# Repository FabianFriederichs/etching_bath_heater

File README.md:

# etching_bath_heater
An AVR 8-Bit µC based etching bath controller including PID controlled heater and agitation.

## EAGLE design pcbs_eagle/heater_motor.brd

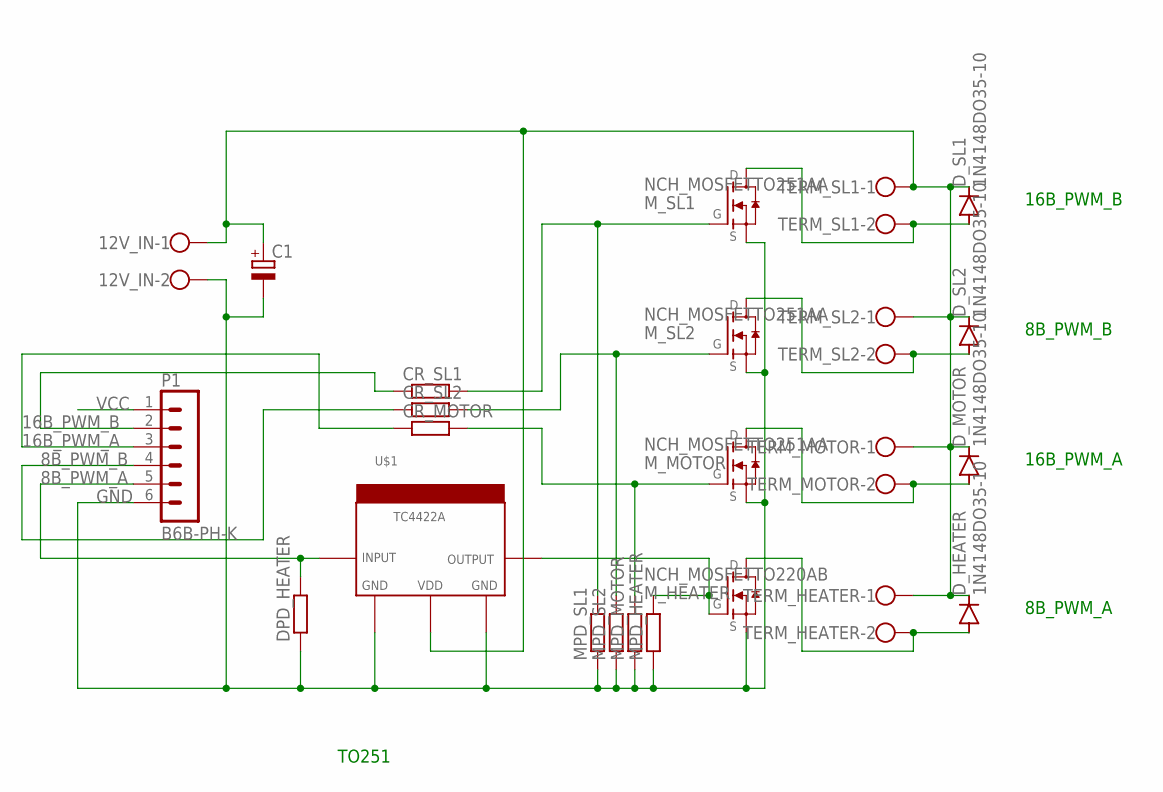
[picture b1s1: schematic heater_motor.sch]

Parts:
12V_IN: W237-102
C1: CPOL-EUE5-10.5; E5-10,5
CR_MOTOR: R-EU_0207/10; 0207/10
CR_SL1, CR_SL2: R-EU_0207/10; 0207/10
DPD_HEATER: R-EU_0207/10; 0207/10
D_HEATER: 1N4148DO35-10; DO35-10
D_MOTOR: 1N4148DO35-10; DO35-10
D_SL1, D_SL2: 1N4148DO35-10; DO35-10
MPD_HEATER: R-EU_0207/10; 0207/10
MPD_MOTOR: R-EU_0207/10; 0207/10
MPD_SL1, MPD_SL2: R-EU_0207/10; 0207/10
M_HEATER: NCH_MOSFETTO220AB; TO220AB
M_MOTOR: NCH_MOSFETTO251AA; TO251AA
M_SL1, M_SL2: NCH_MOSFETTO251AA; TO251AA
P1: B6B-PH-K
TERM_HEATER: W237-102
TERM_MOTOR: W237-102
TERM_SL1, TERM_SL2: W237-102
U$1: TC4422ASPACE_LEGS; TO220-52

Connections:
8B_PWM_A: DPD_HEATER.2, P1.5, U$1.1 (INPUT)
8B_PWM_B: CR_SL2.1, P1.4
16B_PWM_A: CR_MOTOR.1, P1.3
16B_PWM_B: CR_SL1.1, P1.2
GND: 12V_IN.2, C1.-, DPD_HEATER.1, MPD_HEATER.1, MPD_MOTOR.1, MPD_SL1.1, MPD_SL2.1, M_HEATER.3 (S), M_MOTOR.3 (S), M_SL1.3 (S), M_SL2.3 (S), P1.6, U$1.2 (GND1), U$1.4 (GND2)
unnamed: D_HEATER.A, M_HEATER.2 (D), TERM_HEATER.2
unnamed: MPD_HEATER.2, M_HEATER.1 (G), U$1.5 (OUTPUT)
unnamed: D_SL1.A, M_SL1.2 (D), TERM_SL1.2
unnamed: D_SL2.A, M_SL2.2 (D), TERM_SL2.2
unnamed: D_MOTOR.A, M_MOTOR.2 (D), TERM_MOTOR.2
unnamed: CR_MOTOR.2, MPD_MOTOR.2, M_MOTOR.1 (G)
unnamed: CR_SL2.2, MPD_SL2.2, M_SL2.1 (G)
unnamed: CR_SL1.2, MPD_SL1.2, M_SL1.1 (G)
unnamed: 12V_IN.1, C1.+, D_HEATER.C, D_MOTOR.C, D_SL1.C, D_SL2.C, TERM_HEATER.1, TERM_MOTOR.1, TERM_SL1.1, TERM_SL2.1, U$1.3 (VDD)
VCC: P1.1

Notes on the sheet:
TO251
8B_PWM_A
8B_PWM_B
16B_PWM_A
16B_PWM_B

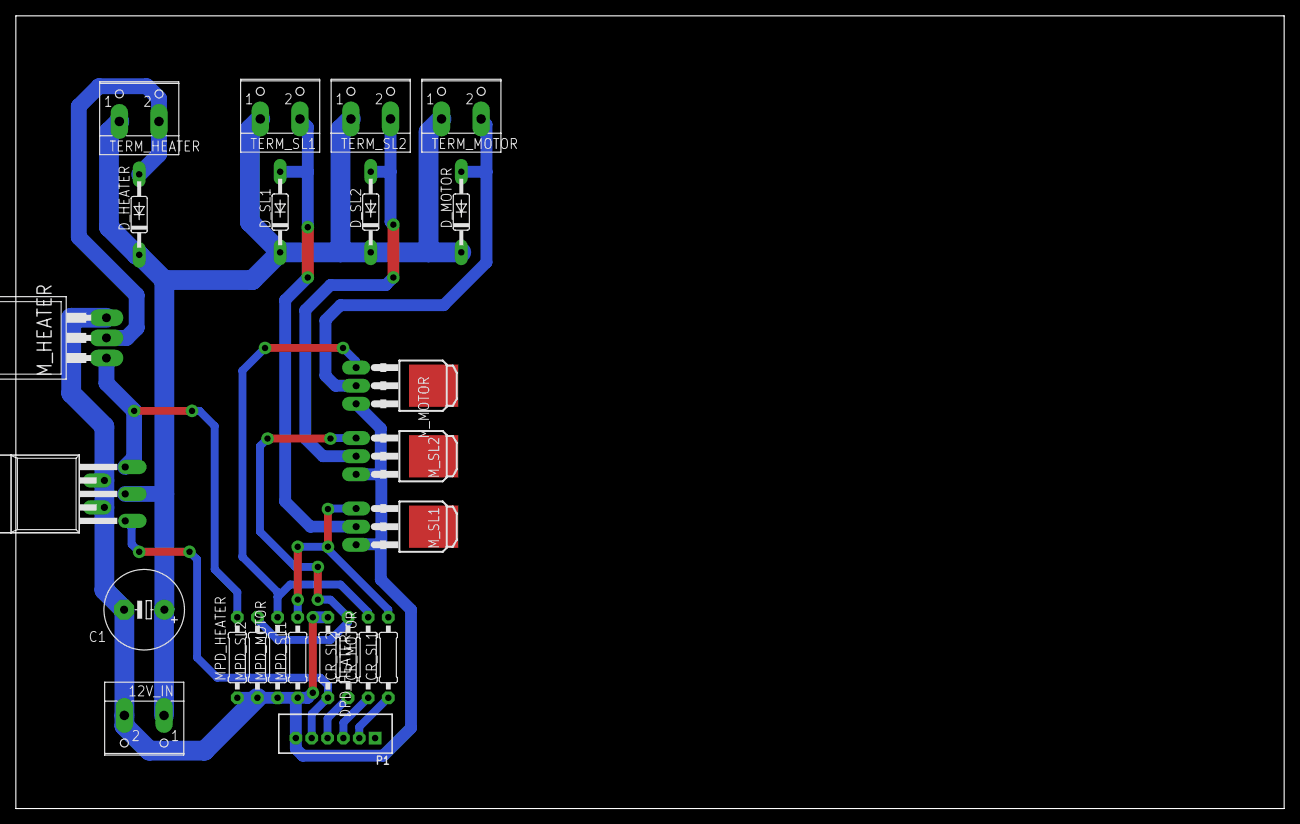
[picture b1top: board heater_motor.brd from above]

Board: 2 copper layers, 160.0 x 100.0 mm, 24 parts (0 on the bottom side), 14 nets.

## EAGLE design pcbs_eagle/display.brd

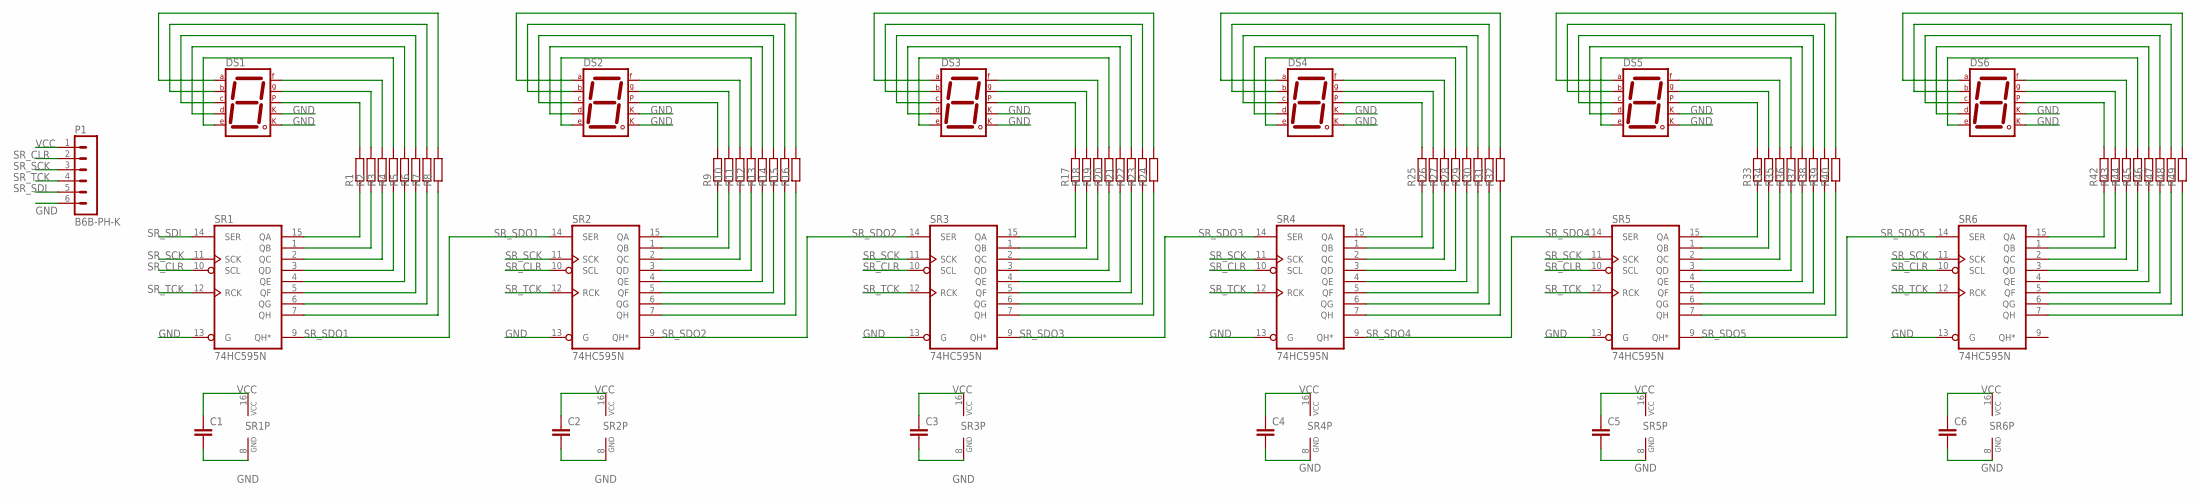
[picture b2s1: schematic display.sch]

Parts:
C1, C2, C3, C4, C5, C6: C-EU025-024X044; C025-024X044
DS1, DS2, DS3, DS4, DS5, DS6: 7SEG-CK; 7SEG-13
P1: B6B-PH-K
R1, R2, R3, R4, R5, R6, R7, R8, R9, R10, R11, R12, R13, R14, R15, R16, R17, R18, R19, R20, R21, R22, R23, R24, R25, R26, R27, R28, R29, R30, R31, R32, R33, R34, R35, R36, R37, R38, R39, R40, R42, R43, R44, R45, R46, R47, R48, R49: R-EU_0207/10; 0207/10
SR1, SR2, SR3, SR4, SR5, SR6: 74HC595N; DIL16

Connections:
GND: C1.2, C2.2, C3.2, C4.2, C5.2, C6.2, DS1.3 (CK1), DS1.8 (CK2), DS2.3 (CK1), DS2.8 (CK2), DS3.3 (CK1), DS3.8 (CK2), DS4.3 (CK1), DS4.8 (CK2), DS5.3 (CK1), DS5.8 (CK2), DS6.3 (CK1), DS6.8 (CK2), P1.6, SR1.8 (GND), SR1.13 (G), SR2.8 (GND), SR2.13 (G), SR3.8 (GND), SR3.13 (G), SR4.8 (GND), SR4.13 (G), SR5.8 (GND), SR5.13 (G), SR6.8 (GND), SR6.13 (G)
unnamed: R1.1, SR1.15 (QA)
unnamed: R2.1, SR1.1 (QB)
unnamed: R3.1, SR1.2 (QC)
unnamed: R4.1, SR1.3 (QD)
unnamed: R5.1, SR1.4 (QE)
unnamed: R6.1, SR1.5 (QF)
unnamed: R7.1, SR1.6 (QG)
unnamed: R8.1, SR1.7 (QH)
unnamed: R9.1, SR2.15 (QA)
unnamed: R10.1, SR2.1 (QB)
unnamed: R11.1, SR2.2 (QC)
unnamed: R12.1, SR2.3 (QD)
unnamed: R13.1, SR2.4 (QE)
unnamed: R14.1, SR2.5 (QF)
unnamed: R15.1, SR2.6 (QG)
unnamed: R16.1, SR2.7 (QH)
unnamed: R17.1, SR3.15 (QA)
unnamed: R18.1, SR3.1 (QB)
unnamed: R19.1, SR3.2 (QC)
unnamed: R20.1, SR3.3 (QD)
unnamed: R21.1, SR3.4 (QE)
unnamed: R22.1, SR3.5 (QF)
unnamed: R23.1, SR3.6 (QG)
unnamed: R24.1, SR3.7 (QH)
unnamed: R25.1, SR4.15 (QA)
unnamed: R26.1, SR4.1 (QB)
unnamed: R27.1, SR4.2 (QC)
unnamed: R28.1, SR4.3 (QD)
unnamed: R29.1, SR4.4 (QE)
unnamed: R30.1, SR4.5 (QF)
unnamed: R31.1, SR4.6 (QG)
unnamed: R32.1, SR4.7 (QH)
unnamed: R33.1, SR5.15 (QA)
unnamed: R34.1, SR5.1 (QB)
unnamed: R35.1, SR5.2 (QC)
unnamed: R36.1, SR5.3 (QD)
unnamed: R37.1, SR5.4 (QE)
unnamed: R38.1, SR5.5 (QF)
unnamed: R39.1, SR5.6 (QG)
unnamed: R40.1, SR5.7 (QH)
unnamed: R42.1, SR6.15 (QA)
unnamed: R43.1, SR6.1 (QB)
unnamed: R44.1, SR6.2 (QC)
unnamed: R45.1, SR6.3 (QD)
unnamed: R46.1, SR6.4 (QE)
unnamed: R47.1, SR6.5 (QF)
unnamed: R48.1, SR6.6 (QG)
unnamed: R49.1, SR6.7 (QH)
unnamed: DS1.5 (DP), R1.2
unnamed: DS1.10 (G), R2.2
unnamed: DS1.9 (F), R3.2
unnamed: DS1.1 (E), R4.2
unnamed: DS1.2 (D), R5.2
unnamed: DS1.4 (C), R6.2
unnamed: DS1.6 (B), R7.2
unnamed: DS1.7 (A), R8.2
unnamed: DS2.5 (DP), R9.2
unnamed: DS2.10 (G), R10.2
unnamed: DS2.9 (F), R11.2
unnamed: DS2.1 (E), R12.2
unnamed: DS2.2 (D), R13.2
unnamed: DS2.4 (C), R14.2
unnamed: DS2.6 (B), R15.2
unnamed: DS2.7 (A), R16.2
unnamed: DS3.5 (DP), R17.2
unnamed: DS3.10 (G), R18.2
unnamed: DS3.9 (F), R19.2
unnamed: DS3.1 (E), R20.2
unnamed: DS3.2 (D), R21.2
unnamed: DS3.4 (C), R22.2
unnamed: DS3.6 (B), R23.2
unnamed: DS3.7 (A), R24.2
unnamed: DS4.5 (DP), R25.2
unnamed: DS4.10 (G), R26.2
unnamed: DS4.9 (F), R27.2
unnamed: DS4.1 (E), R28.2
unnamed: DS4.2 (D), R29.2
unnamed: DS4.4 (C), R30.2
unnamed: DS4.6 (B), R31.2
unnamed: DS4.7 (A), R32.2
unnamed: DS5.5 (DP), R33.2
unnamed: DS5.10 (G), R34.2
unnamed: DS5.9 (F), R35.2
unnamed: DS5.1 (E), R36.2
unnamed: DS5.2 (D), R37.2
unnamed: DS5.4 (C), R38.2
unnamed: DS5.6 (B), R39.2
unnamed: DS5.7 (A), R40.2
unnamed: DS6.5 (DP), R42.2
unnamed: DS6.10 (G), R43.2
unnamed: DS6.9 (F), R44.2
unnamed: DS6.1 (E), R45.2
unnamed: DS6.2 (D), R46.2
unnamed: DS6.4 (C), R47.2
unnamed: DS6.6 (B), R48.2
unnamed: DS6.7 (A), R49.2
SR_CLR: P1.2, SR1.10 (SCL), SR2.10 (SCL), SR3.10 (SCL), SR4.10 (SCL), SR5.10 (SCL), SR6.10 (SCL)
SR_SCK: P1.3, SR1.11 (SCK), SR2.11 (SCK), SR3.11 (SCK), SR4.11 (SCK), SR5.11 (SCK), SR6.11 (SCK)
SR_SDI: P1.5, SR1.14 (SER)
SR_SDO1: SR1.9 (QH*), SR2.14 (SER)
SR_SDO2: SR2.9 (QH*), SR3.14 (SER)
SR_SDO3: SR3.9 (QH*), SR4.14 (SER)
SR_SDO4: SR4.9 (QH*), SR5.14 (SER)
SR_SDO5: SR5.9 (QH*), SR6.14 (SER)
SR_TCK: P1.4, SR1.12 (RCK), SR2.12 (RCK), SR3.12 (RCK), SR4.12 (RCK), SR5.12 (RCK), SR6.12 (RCK)
VCC: C1.1, C2.1, C3.1, C4.1, C5.1, C6.1, P1.1, SR1.16 (VCC), SR2.16 (VCC), SR3.16 (VCC), SR4.16 (VCC), SR5.16 (VCC), SR6.16 (VCC)

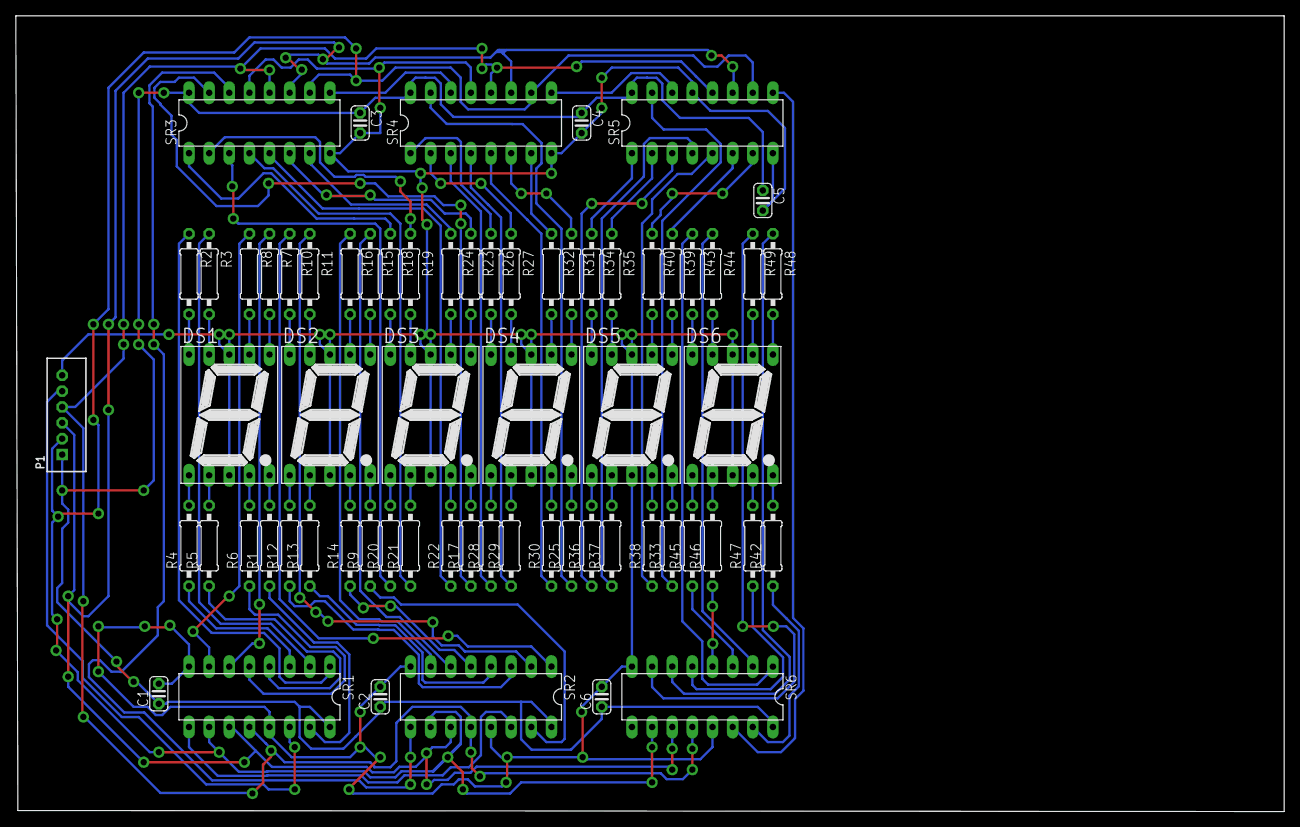
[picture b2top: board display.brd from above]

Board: 2 copper layers, 160.0 x 100.4 mm, 67 parts (0 on the bottom side), 107 nets.

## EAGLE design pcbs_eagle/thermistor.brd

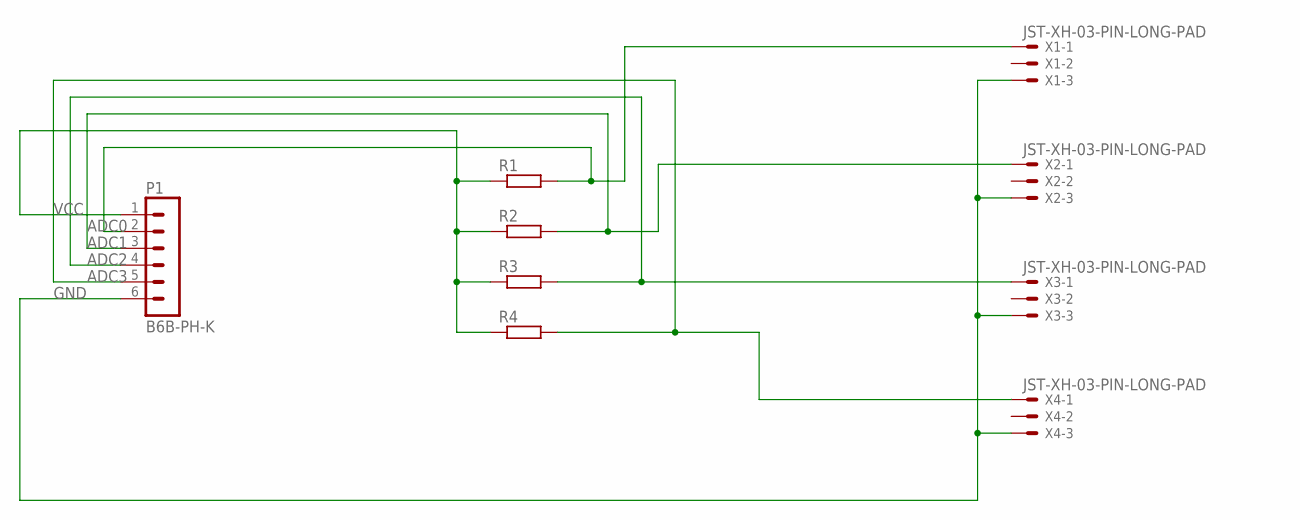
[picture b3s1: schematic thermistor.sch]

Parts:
P1: B6B-PH-K
R1, R2, R3, R4: R-EU_0207/10; 0207/10
X1, X2, X3, X4: JST-XH-03-PIN-LONG-PAD; JST-XH-03-PACKAGE-LONG-PAD

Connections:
ADC0: P1.2, R1.2, X1.1
ADC1: P1.3, R2.2, X2.1
ADC2: P1.4, R3.2, X3.1
ADC3: P1.5, R4.2, X4.1
GND: P1.6, X1.3, X2.3, X3.3, X4.3
VCC: P1.1, R1.1, R2.1, R3.1, R4.1

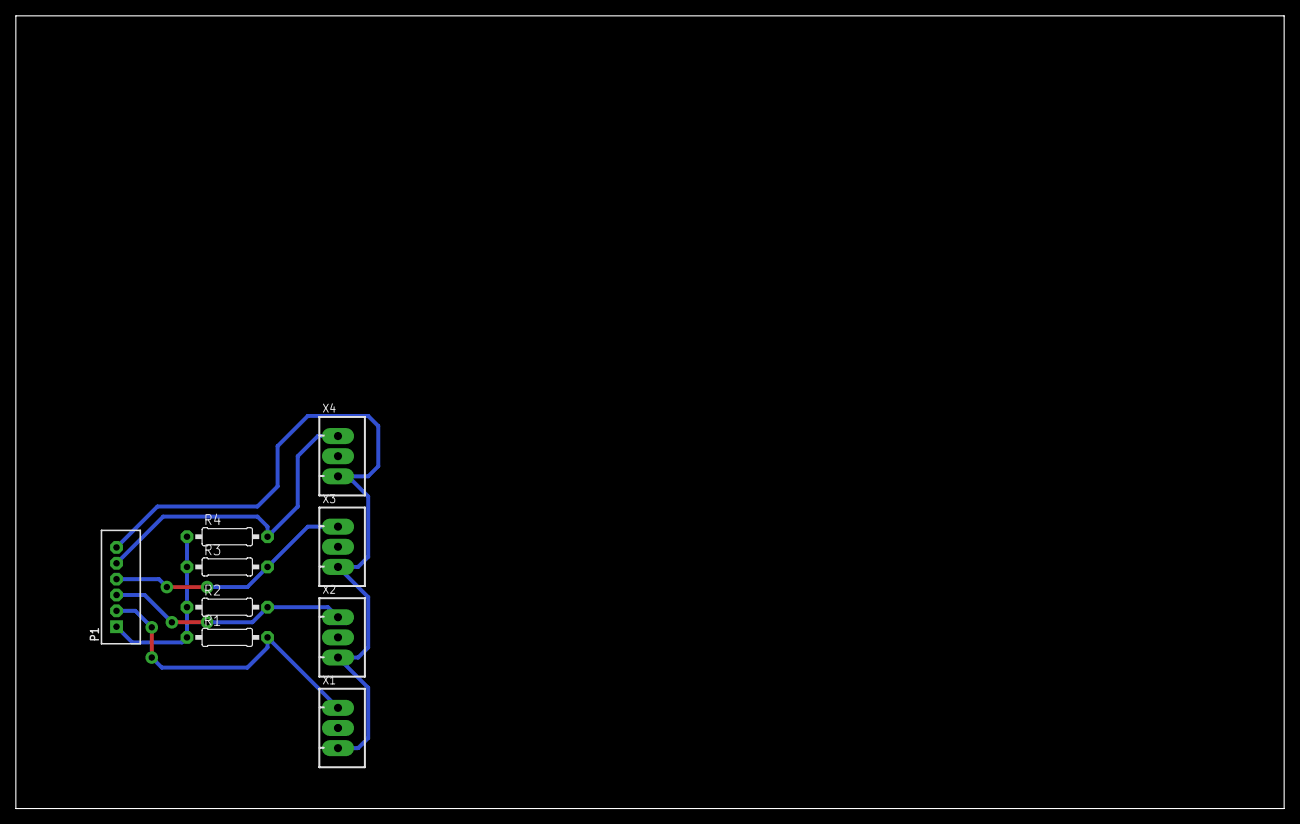
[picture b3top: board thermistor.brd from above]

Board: 2 copper layers, 160.0 x 100.0 mm, 9 parts (0 on the bottom side), 6 nets.

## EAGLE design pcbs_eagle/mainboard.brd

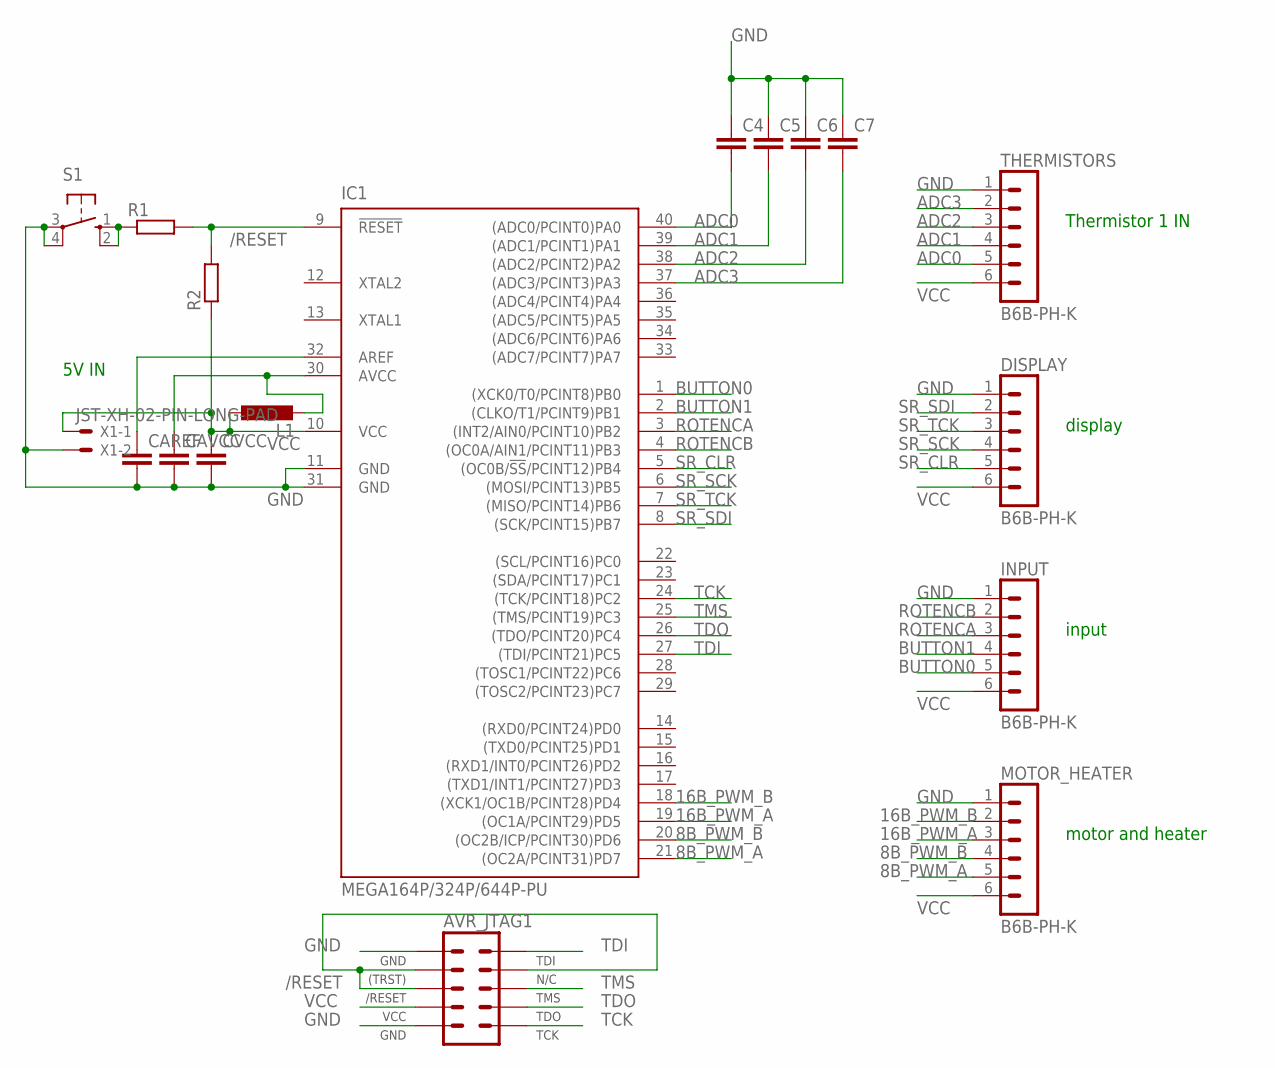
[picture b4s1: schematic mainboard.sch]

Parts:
AVR_JTAG1: AVR_JTAG_2X5/IN; AVR_JTAG_2X5
C4, C5, C6, C7: C-EU025-024X044; C025-024X044
CAREF: C-EU025-024X044; C025-024X044
CAVCC: C-EU025-024X044; C025-024X044
CVCC: C-EU025-024X044; C025-024X044
DISPLAY: B6B-PH-K
IC1: MEGA164P/324P/644P-PU; DIL40
INPUT: B6B-PH-K
L1: L-EU0207/10; 0207/10
MOTOR_HEATER: B6B-PH-K
R1, R2: R-EU_0207/10; 0207/10
S1: 10-XX; B3F-10XX
THERMISTORS: B6B-PH-K
X1: JST-XH-02-PIN-LONG-PAD; JST-XH-02-PACKAGE-LONG-PAD

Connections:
8B_PWM_A: IC1.21 ((OC2A/PCINT31)PD7), MOTOR_HEATER.5
8B_PWM_B: IC1.20 ((OC2B/ICP/PCINT30)PD6), MOTOR_HEATER.4
16B_PWM_A: IC1.19 ((OC1A/PCINT29)PD5), MOTOR_HEATER.3
16B_PWM_B: IC1.18 ((XCK1/OC1B/PCINT28)PD4), MOTOR_HEATER.2
/RESET: AVR_JTAG1.6 (/RESET), AVR_JTAG1.7 (N/C), AVR_JTAG1.8 ((TRST)), IC1.9 (!RESET), R1.2, R2.2
ADC0: C4.2, IC1.40 ((ADC0/PCINT0)PA0), THERMISTORS.5
ADC1: C5.2, IC1.39 ((ADC1/PCINT1)PA1), THERMISTORS.4
ADC2: C6.2, IC1.38 ((ADC2/PCINT2)PA2), THERMISTORS.3
ADC3: C7.2, IC1.37 ((ADC3/PCINT3)PA3), THERMISTORS.2
BUTTON0: IC1.1 ((XCK0/T0/PCINT8)PB0), INPUT.5
BUTTON1: IC1.2 ((CLKO/T1/PCINT9)PB1), INPUT.4
GND: AVR_JTAG1.2 (GND1), AVR_JTAG1.10 (GND2), C4.1, C5.1, C6.1, C7.1, CAREF.2, CAVCC.2, CVCC.2, DISPLAY.1, IC1.11 (GND), IC1.31 (GND), INPUT.1, MOTOR_HEATER.1, S1.3, S1.4 (P1), THERMISTORS.1, X1.2
unnamed: CAVCC.1, IC1.30 (AVCC), L1.2
unnamed: R1.1, S1.1 (S), S1.2 (S1)
unnamed: CAREF.1, IC1.32 (AREF)
ROTENCA: IC1.3 ((INT2/AIN0/PCINT10)PB2), INPUT.3
ROTENCB: IC1.4 ((OC0A/AIN1/PCINT11)PB3), INPUT.2
SR_CLR: DISPLAY.5, IC1.5 ((OC0B/!SS!/PCINT12)PB4)
SR_SCK: DISPLAY.4, IC1.6 ((MOSI/PCINT13)PB5)
SR_SDI: DISPLAY.2, IC1.8 ((SCK/PCINT15)PB7)
SR_TCK: DISPLAY.3, IC1.7 ((MISO/PCINT14)PB6)
TCK: AVR_JTAG1.1 (TCK), IC1.24 ((TCK/PCINT18)PC2)
TDI: AVR_JTAG1.9 (TDI), IC1.27 ((TDI/PCINT21)PC5)
TDO: AVR_JTAG1.3 (TDO), IC1.26 ((TDO/PCINT20)PC4)
TMS: AVR_JTAG1.5 (TMS), IC1.25 ((TMS/PCINT19)PC3)
VCC: AVR_JTAG1.4 (VCC), CVCC.1, DISPLAY.6, IC1.10 (VCC), INPUT.6, L1.1, MOTOR_HEATER.6, R2.1, THERMISTORS.6, X1.1

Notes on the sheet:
5V IN
Thermistor 1 IN
display
input
motor and heater

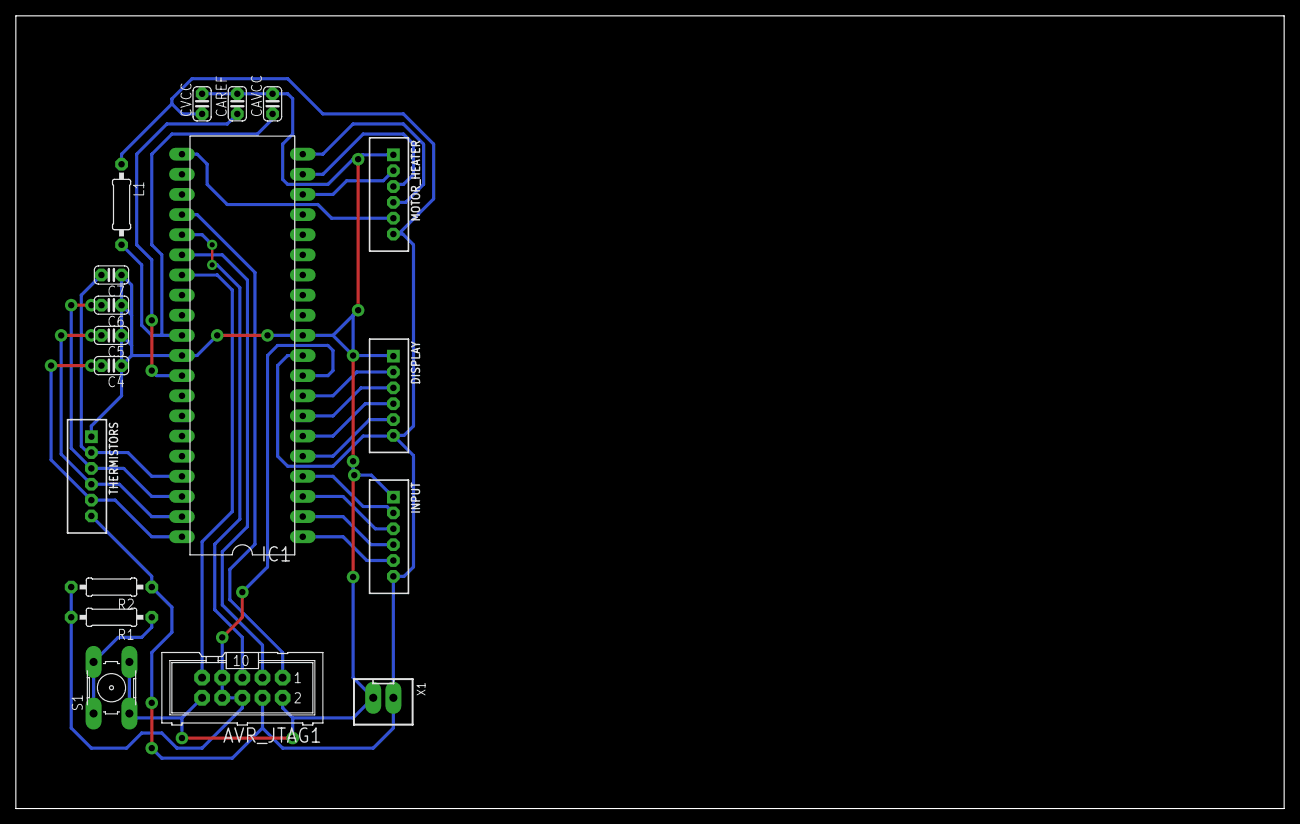
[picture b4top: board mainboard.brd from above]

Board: 2 copper layers, 160.0 x 100.0 mm, 18 parts (0 on the bottom side), 26 nets.

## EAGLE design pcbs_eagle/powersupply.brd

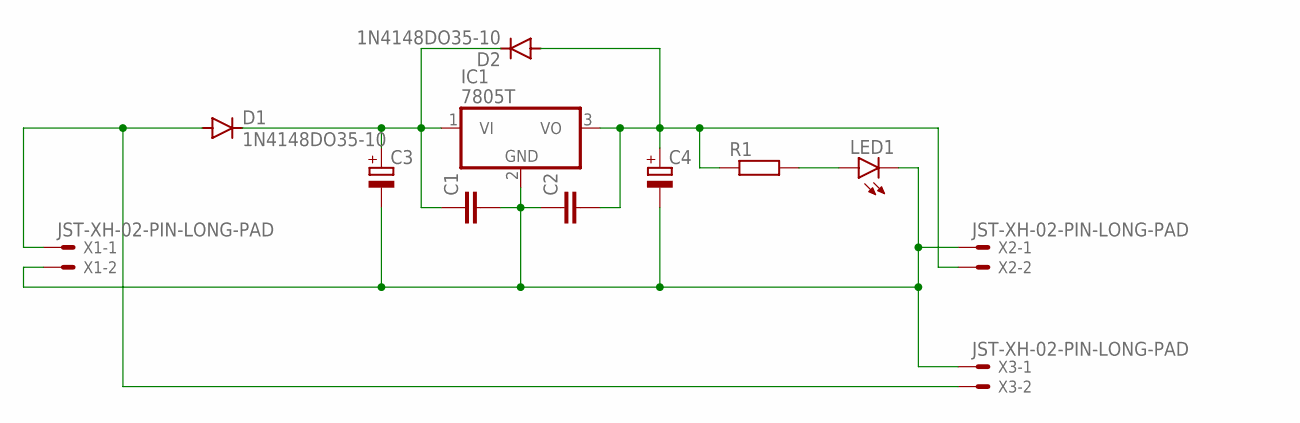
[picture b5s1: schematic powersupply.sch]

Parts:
C1, C2: C-EU025-024X044; C025-024X044
C3, C4: CPOL-EUE2,5-6E; E2,5-6E
D1, D2: 1N4148DO35-10; DO35-10
IC1: 7805T; TO220H
LED1: LED5MM
R1: R-EU_0207/10; 0207/10
X1, X2, X3: JST-XH-02-PIN-LONG-PAD; JST-XH-02-PACKAGE-LONG-PAD

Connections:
GND: C1.2, C2.1, C3.-, C4.-, IC1.2 (GND), LED1.K (C), X1.2, X2.1, X3.1
unnamed: D1.A, X1.1, X3.2
unnamed: C1.1, C3.+, D1.C, D2.C, IC1.1 (VI)
unnamed: C2.2, C4.+, D2.A, IC1.3 (VO), R1.1, X2.2
unnamed: LED1.A, R1.2

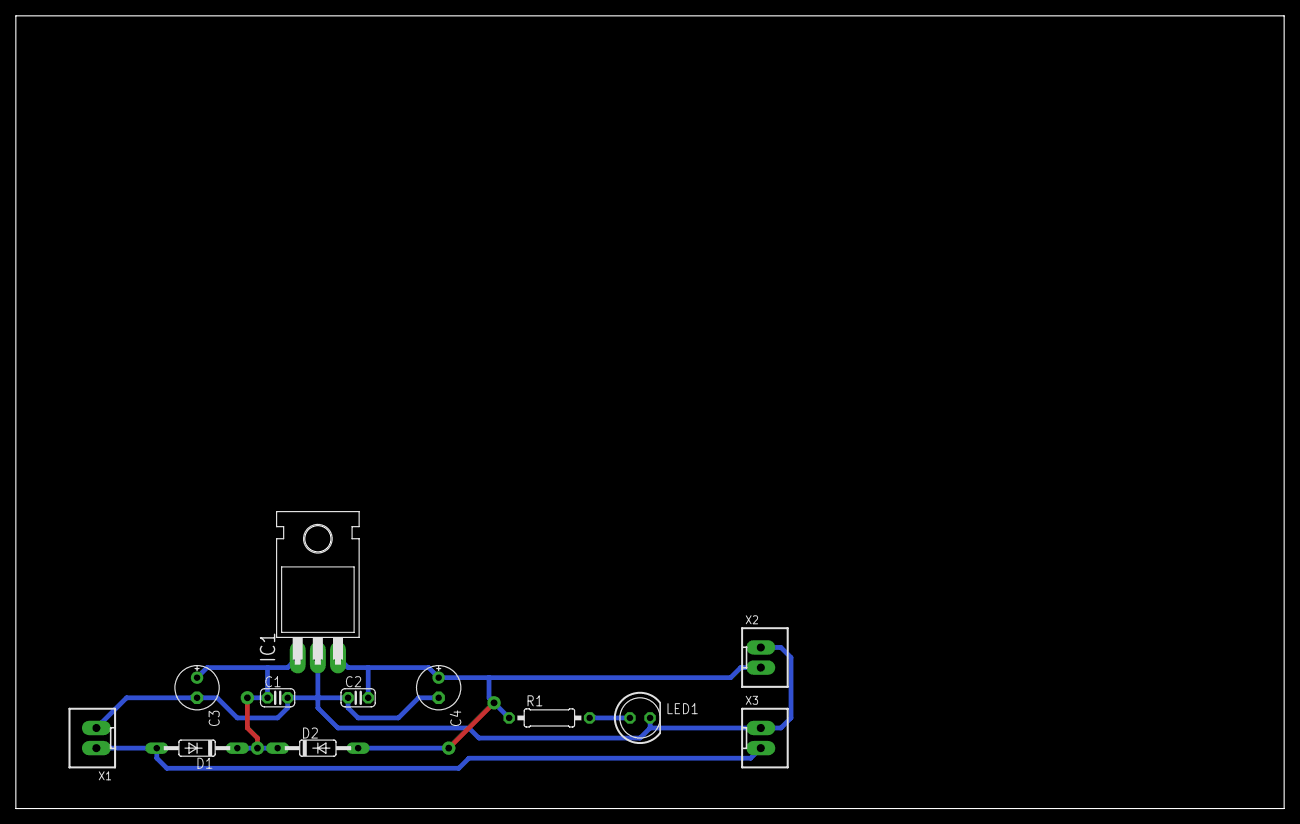
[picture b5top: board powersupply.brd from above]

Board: 2 copper layers, 160.0 x 100.0 mm, 12 parts (0 on the bottom side), 5 nets.

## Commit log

2020-02-18 fixed eeprom menu strings
2020-02-18 added thermal runaway protection
2020-02-18 fixed pid d bug
2020-02-18 added adjustable i-clamping
2020-02-20 ground planes
2020-02-22 fixed menu bug
2020-02-25 changed pid derivative to PV-based derivative
2020-02-26 changed pid parameterization
2020-02-26 finished pid stuff. needs to be tested.
2020-02-28 Fixed floating point display.
2020-02-28 added exponential smoothing of D-term
2020-05-24 increased heater max temp
2020-07-01 Create LICENSE
2020-07-02 stuff
2020-09-13 Heater case in progress...
2020-09-14 Chamfers
2020-09-15 Case V1 finished
2020-09-16 Modified strain relief plug for printing with PP
2020-09-18 Case stuff
2020-09-23 Config stuff
2020-09-23 gcode
2020-09-23 fan control
2020-09-23 strain relief plugs are working nicely
2020-09-23 fan control works
2020-09-28 knob
2020-09-29 more stuff
2020-10-03 created remaining case parts
2020-10-12 reduced heater pwm frequency and adjusted thermal runaway protection params

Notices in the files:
parts and their libraries:
con-jst-ph: Copyright (C) 2016, Bob Starr
